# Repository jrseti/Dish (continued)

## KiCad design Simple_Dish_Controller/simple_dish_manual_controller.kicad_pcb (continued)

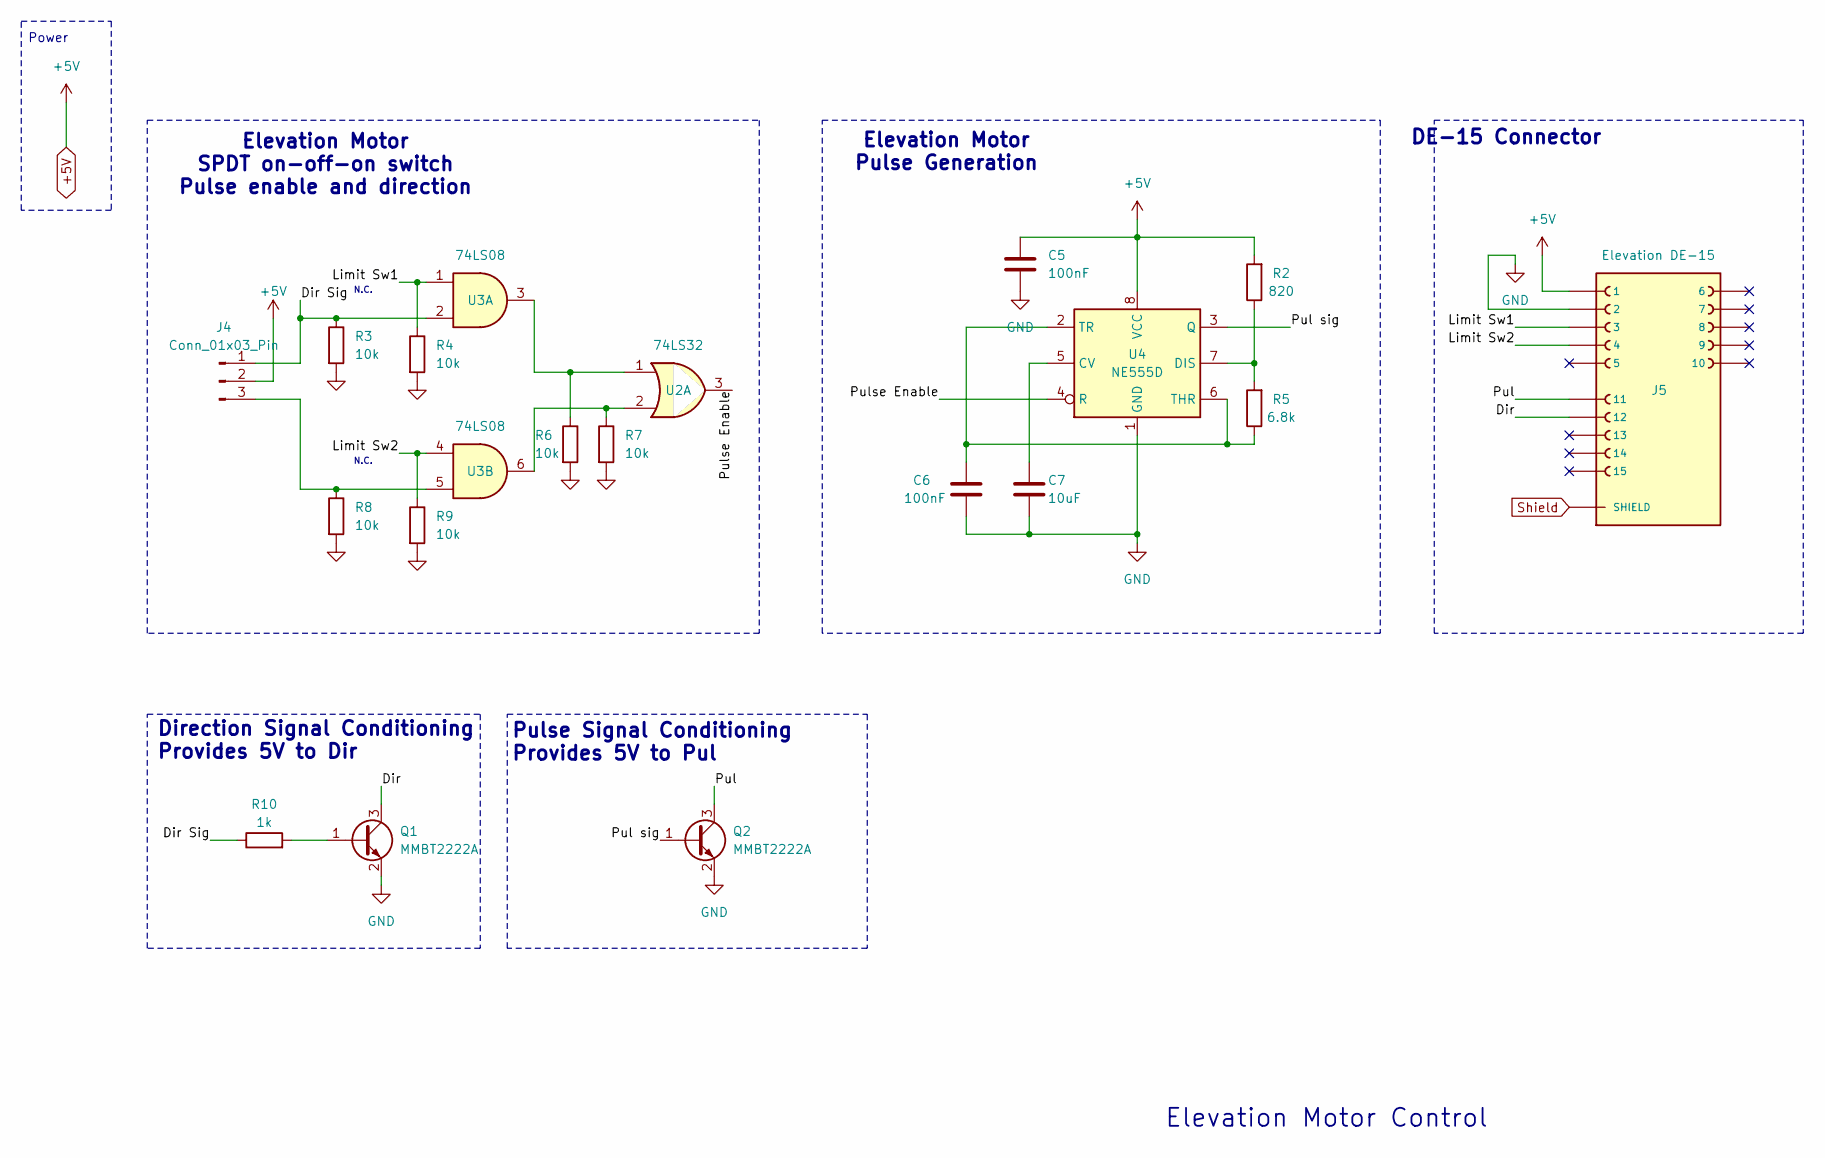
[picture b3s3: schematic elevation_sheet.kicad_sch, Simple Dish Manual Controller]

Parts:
C5, C6: 100nF; C_1206_3216Metric; LCSC Part C24497
C7: 10uF; C_1206_3216Metric; LCSC Part C13585
J4: Conn_01x03_Pin; PinHeader_1x03_P2.54mm_Vertical
J5: Elevation DE-15; DE15_VGA_FEMALE_CONN; PARTREV 1; DigiKey_Part_Number L77HDE15SD1CH4FVGA-ND
Q1, Q2: MMBT2222A; SOT-23; LCSC Part C8512
R2: 820; R_1206_3216Metric; LCSC Part C17984
R3, R4, R6, R7, R8, R9: 10k; R_1206_3216Metric; LCSC Part C17902
R5: 6.8k; R_1206_3216Metric; LCSC Part C2907522
R10: 1k; R_1206_3216Metric; LCSC Part C4410
U2: 74LS32; SOIC-14_3.9x8.7mm_P1.27mm; LCSC Part C116812
U3: 74LS08; SOIC-14_3.9x8.7mm_P1.27mm; LCSC Part C6802
U4: NE555D; SOIC-8_3.9x4.9mm_P1.27mm; LCSC Part C234230

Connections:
+5V: C5.1, J4.2, J5.1, R2.2, U4.8 (VCC); also elsewhere on the board
/Elevation/Dir: J5.12, Q1.3 (C)
/Elevation/Dir Sig: J4.1, R3.1, R10.1, U3.2
/Elevation/Limit Sw1: J5.3, R4.1, U3.1
/Elevation/Limit Sw2: J5.4, R9.1, U3.4
/Elevation/Pul: J5.11, Q2.3 (C)
/Elevation/Pul sig: Q2.1 (B), U4.3 (Q)
/Elevation/Pulse Enable: U2.3, U4.4 (R)
GND: C5.2, C6.2, C7.2, J5.2, Q1.2 (E), Q2.2 (E), R3.2, R4.2, R6.2, R7.2, R8.2, R9.2, U4.1 (GND); also elsewhere on the board
unnamed: J4.3, R8.1, U3.5
unnamed: Q1.1 (B), R10.2
unnamed: R6.1, U2.1, U3.3
unnamed: R7.1, U2.2, U3.6
unnamed: C7.1, U4.5 (CV)
unnamed: R2.1, R5.2, U4.7 (DIS)
unnamed: C6.1, R5.1, U4.2 (TR), U4.6 (THR)
Shield: J5.SH1 (SHIELD), J5.SH2 (SHIELD); also elsewhere on the board

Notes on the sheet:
DE-15 Connector
Elevation Motor Control
Power
N.C.
Pulse Signal Conditioning Provides 5V to Pul
Elevation Motor SPDT on-off-on switch Pulse enable and direction
Elevation Motor Pulse Generation
Direction Signal Conditioning Provides 5V to Dir

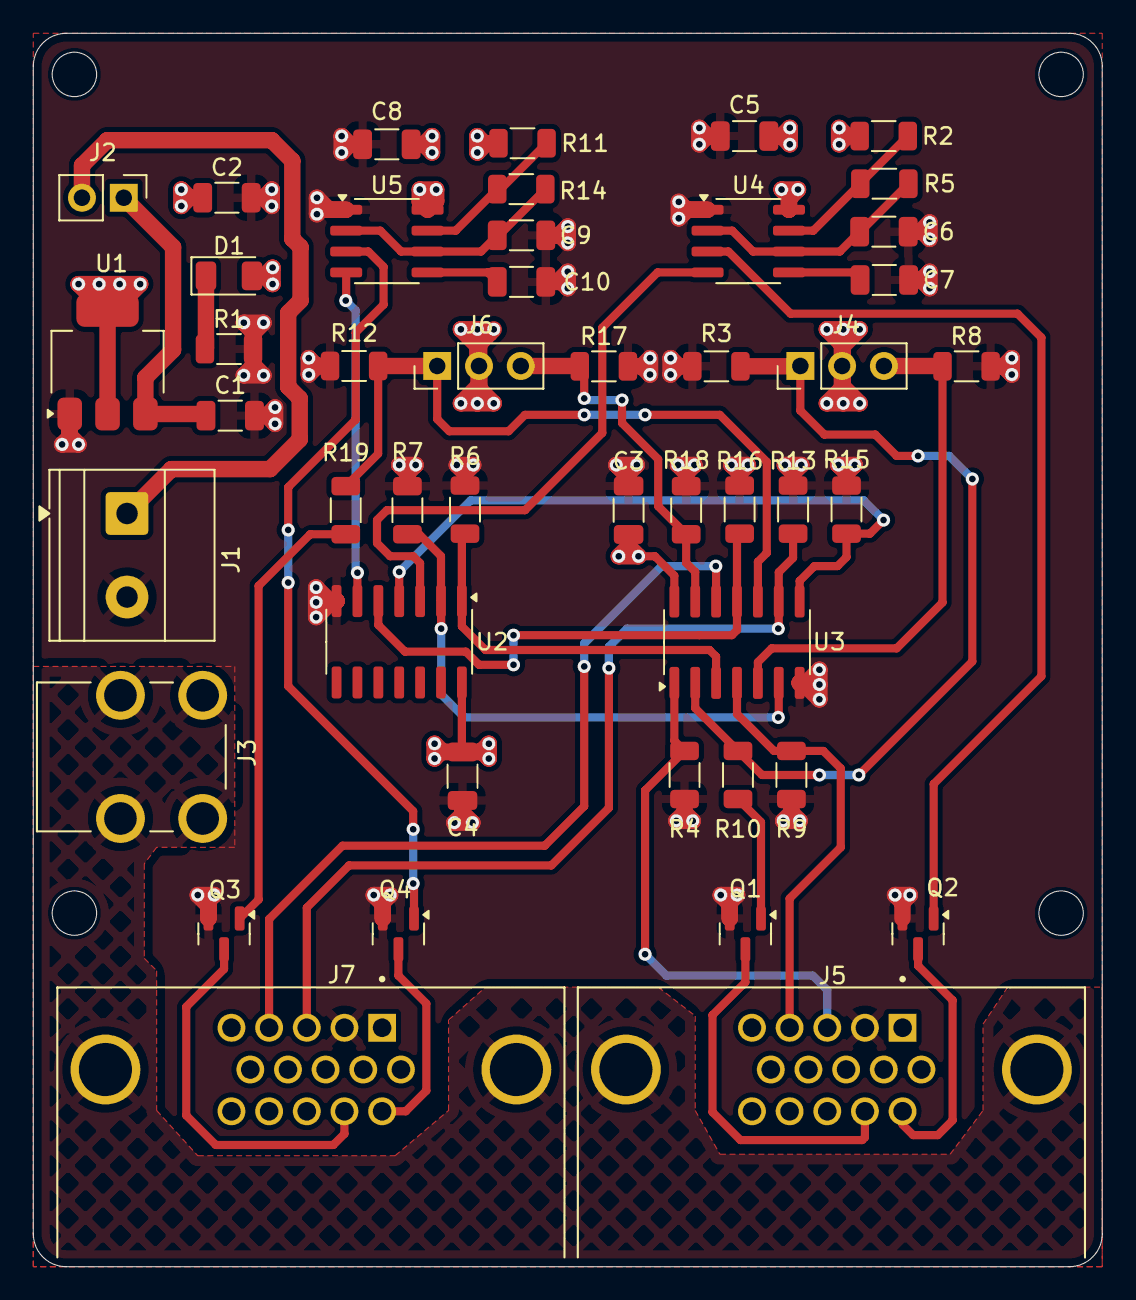
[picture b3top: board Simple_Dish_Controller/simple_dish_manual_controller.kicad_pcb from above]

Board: 4 copper layers, 65.0 x 75.0 mm, 50 parts (0 on the bottom side), 34 nets.

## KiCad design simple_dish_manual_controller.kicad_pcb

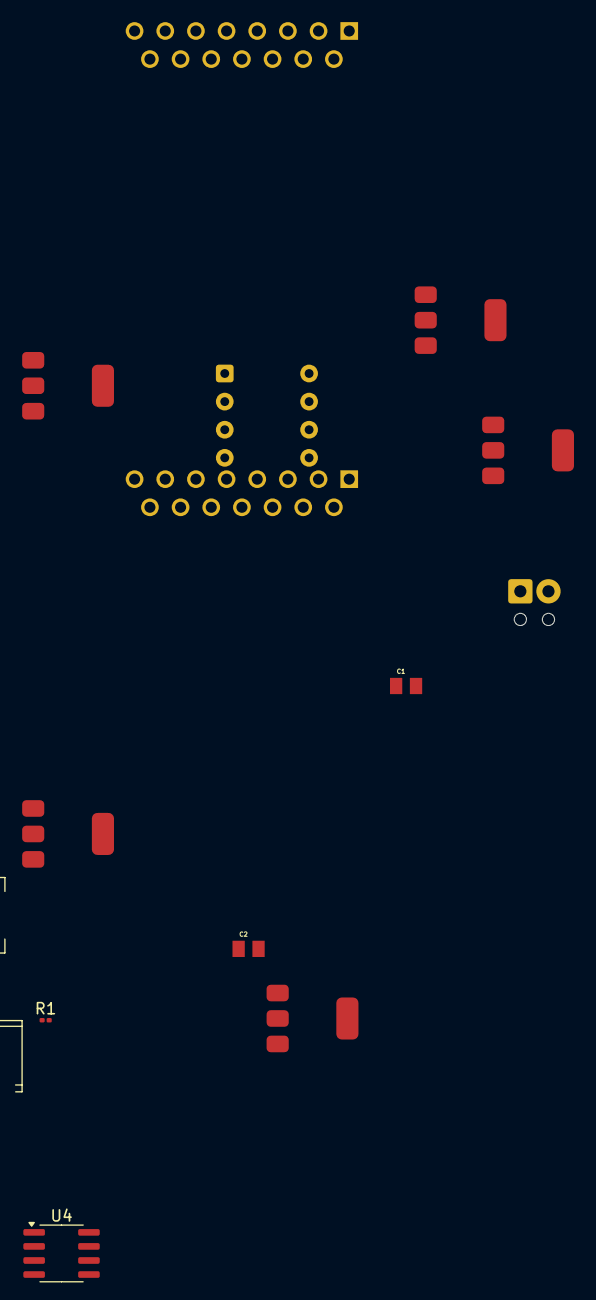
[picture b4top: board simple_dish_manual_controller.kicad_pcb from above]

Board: 2 copper layers, 13 parts (0 on the bottom side), 11 nets, no tracks yet.

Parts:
C1, C2: 22uF; CAPC2012X100N
J1: Screw_Terminal_01x02; TerminalBlock_Phoenix_MPT-0,5-2-2.54_1x02_P2.54mm_Horizontal
J2, J3: DA15_Socket; DSUB-15_Socket_Horizontal_P2.77x2.54mm_EdgePinOffset9.40mm
Q1, Q2, Q3, Q4: PZT2222A; SOT-223-3_TabPin2
R1: 1k5; R_0201_0603Metric
U1: AMS1117-5.0; SOT-223-3_TabPin2
U4: ICM7555xP; SOIC-8_3.9x4.9mm_P1.27mm
U5: ICM7555xP; DIP-8_W7.62mm

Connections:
+5V: C2.2, J2.5, J2.8, J3.5, J3.8, U1.2 (VO), U4.8 (VCC), U5.8 (VCC)
/Azimuth/Dir: J3.9, Q3.2 (C)
/Azimuth/Pul: J3.2, Q4.2 (C)
/Elevation/Dir: J2.9, Q2.2 (C)
/Elevation/Pul: J2.2, Q1.2 (C)
/IN_5VDC_SWITCH: C1.2, U1.3 (VI)
GND: C1.1, C2.1, J1.2, J2.1, J2.15, J3.1, J3.15, Q1.3 (E), Q2.3 (E), Q3.3 (E), Q4.3 (E), R1.2, U1.1 (GND), U4.1 (GND), U5.1 (GND)
unnamed: Q1.1 (B), U4.3 (Q)
unnamed: Q4.1 (B), U5.3 (Q)
unnamed: U4.2 (TR), U4.6 (THR)
unnamed: U5.2 (TR), U5.6 (THR)

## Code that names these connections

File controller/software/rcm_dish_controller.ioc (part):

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Mcu.Name=STM32G474R(B-C-E)Tx
Mcu.Package=LQFP64
Mcu.UserName=STM32G474RETx
PA0.GPIOParameters=GPIO_Label
PA0.GPIO_Label=ENC1_A
PA0.Signal=S_TIM2_CH1
PA1.GPIOParameters=GPIO_Label
PA1.GPIO_Label=ENC1_B
PA1.Signal=S_TIM2_CH2
PA10.GPIOParameters=GPIO_PuPd,GPIO_Label
PA10.GPIO_Label=SW2
PA10.GPIO_PuPd=GPIO_PULLUP
PA10.Signal=GPIO_Input
PA11.Mode=FDCAN_Activate
PA11.Signal=FDCAN1_RX
PA12.Mode=FDCAN_Activate
PA12.Signal=FDCAN1_TX
PA13.Mode=Trace_Asynchronous_SW
PA13.Signal=SYS_JTMS-SWDIO
PA14.Mode=Trace_Asynchronous_SW
PA14.Signal=SYS_JTCK-SWCLK
PA15.GPIOParameters=GPIO_PuPd,GPIO_Label
PA15.GPIO_Label=USER_SW_4
PA15.GPIO_PuPd=GPIO_PULLUP
PA15.Signal=GPIO_Input
PA2.GPIOParameters=GPIO_PuPd,GPIO_Label
PA2.GPIO_Label=ENC1_Z
PA2.GPIO_PuPd=GPIO_PULLUP
PA2.Signal=GPXTI2
PA3.GPIOParameters=GPIO_PuPd,GPIO_Label
PA3.GPIO_Label=LIMIT1_SW1
PA3.GPIO_PuPd=GPIO_PULLUP
PA3.Signal=GPIO_Input
PA4.GPIOParameters=GPIO_PuPd,GPIO_Label
PA4.GPIO_Label=LIMIT1_SW2
PA4.GPIO_PuPd=GPIO_PULLUP
PA4.Signal=GPIO_Input
PA5.GPIOParameters=GPIO_PuPd,GPIO_Label
PA5.GPIO_Label=LIMIT2_SW1
PA5.GPIO_PuPd=GPIO_PULLUP
PA5.Signal=GPIO_Input
PA6.GPIOParameters=GPIO_Label
PA6.GPIO_Label=PUL1
PA6.Signal=S_TIM16_CH1
PA7.GPIOParameters=GPIO_PuPd,GPIO_Label
PA7.GPIO_Label=LIMIT2_SW2
PA7.GPIO_PuPd=GPIO_PULLUP
PA7.Signal=GPIO_Input
PA8.GPIOParameters=GPIO_PuPd,GPIO_Label
PA8.GPIO_Label=SW4
PA8.GPIO_PuPd=GPIO_PULLUP
PA8.Signal=GPIO_Input
PA9.GPIOParameters=GPIO_PuPd,GPIO_Label
PA9.GPIO_Label=SW3
PA9.GPIO_PuPd=GPIO_PULLUP
PA9.Signal=GPIO_Input
PB0.GPIOParameters=GPIO_Label
PB0.GPIO_Label=PUL2
PB0.Signal=S_TIM3_CH3
PB1.GPIOParameters=GPIO_Label
PB1.GPIO_Label=DIR2
PB1.Signal=GPIO_Output
PB10.GPIOParameters=GPIO_Label
PB10.GPIO_Label=GPS_RX_MCU
PB10.Mode=Asynchronous
PB10.Signal=LPUART1_RX
PB11.GPIOParameters=GPIO_Label
PB11.GPIO_Label=GPS_TX_MCU
PB11.Mode=Asynchronous
PB11.Signal=LPUART1_TX
PB12.GPIOParameters=GPIO_Speed,GPIO_Label,GPIO_ModeDefaultOutputPP
PB12.GPIO_Label=FLASH_CS
PB12.GPIO_ModeDefaultOutputPP=GPIO_MODE_OUTPUT_PP
PB12.GPIO_Speed=GPIO_SPEED_FREQ_HIGH
PB12.Signal=GPIO_Output
PB13.Mode=Full_Duplex_Master
PB13.Signal=SPI2_SCK
PB14.Mode=Full_Duplex_Master
PB14.Signal=SPI2_MISO
PB15.Mode=Full_Duplex_Master
PB15.Signal=SPI2_MOSI
PB2.GPIOParameters=GPIO_Label
PB2.GPIO_Label=ENABLE2
PB2.Signal=GPIO_Output
PB3.Mode=Trace_Asynchronous_SW
PB3.Signal=SYS_JTDO-SWO
PB4.GPIOParameters=GPIO_Label
PB4.GPIO_Label=FAN
PB4.Signal=GPIO_Output
PB6.GPIOParameters=GPIO_Label
PB6.GPIO_Label=CM4_TX
PB6.Mode=Asynchronous
PB6.Signal=USART1_TX
PB7.GPIOParameters=GPIO_Label
PB7.GPIO_Label=CM4_RX
PB7.Mode=Asynchronous
PB7.Signal=USART1_RX
PB9.GPIOParameters=GPIO_Label
PB9.GPIO_Label=GPS_1PPS
PB9.Signal=S_TIM17_CH1
PC0.GPIOParameters=GPIO_Label
PC0.GPIO_Label=ENC2_A
PC0.Signal=S_TIM1_CH1
PC1.GPIOParameters=GPIO_Label
PC1.GPIO_Label=ENC2_B
PC1.Signal=S_TIM1_CH2
PC10.GPIOParameters=GPIO_PuPd,GPIO_Label
PC10.GPIO_Label=SW1
PC10.GPIO_PuPd=GPIO_PULLUP
PC10.Signal=GPIO_Input
PC11.GPIOParameters=GPIO_Label
PC11.GPIO_Label=STATUS_LED
PC11.Signal=GPIO_Output
PC2.GPIOParameters=GPIO_PuPd,GPIO_Label
PC2.GPIO_Label=USER_SW_1
PC2.GPIO_PuPd=GPIO_PULLUP
PC2.Signal=GPIO_Input
PC3.GPIOParameters=GPIO_PuPd,GPIO_Label
PC3.GPIO_Label=ENC2_Z
PC3.GPIO_PuPd=GPIO_PULLUP
PC3.Signal=GPXTI3
PC4.GPIOParameters=GPIO_Label
PC4.GPIO_Label=DIR1
PC4.Signal=GPIO_Output
PC5.GPIOParameters=GPIO_Label
PC5.GPIO_Label=ENABLE1
PC5.Signal=GPIO_Output
PC6.Mode=I2C
PC6.Signal=I2C4_SCL
PC7.Mode=I2C
PC7.Signal=I2C4_SDA
PC8.GPIOParameters=GPIO_PuPd,GPIO_Label
PC8.GPIO_Label=USER_SW_2
PC8.GPIO_PuPd=GPIO_PULLUP
PC8.Signal=GPIO_Input
PC9.GPIOParameters=GPIO_PuPd,GPIO_Label
PC9.GPIO_Label=USER_SW_3
PC9.GPIO_PuPd=GPIO_PULLUP
PC9.Signal=GPIO_Input
PD2.GPIOParameters=GPIO_PuPd,GPIO_Label,GPIO_ModeDefaultOutputPP
PD2.GPIO_Label=MCU_nIRQ
PD2.GPIO_ModeDefaultOutputPP=GPIO_MODE_OUTPUT_OD
PD2.GPIO_PuPd=GPIO_NOPULL
PD2.Signal=GPIO_Output
PF0-OSC_IN.Mode=HSE-External-Oscillator
PF0-OSC_IN.Signal=RCC_OSC_IN
PF1-OSC_OUT.Mode=HSE-External-Oscillator
PF1-OSC_OUT.Signal=RCC_OSC_OUT
RCC.HSE_VALUE=16000000
RCC.SYSCLKFreq_VALUE=170000000
RCC.SYSCLKSource=RCC_SYSCLKSOURCE_PLLCLK
board=custom

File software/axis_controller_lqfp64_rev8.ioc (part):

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Mcu.Name=STM32G474R(B-C-E)Tx
Mcu.Package=LQFP64
Mcu.UserName=STM32G474RETx
PA0.GPIOParameters=GPIO_Label
PA0.GPIO_Label=ENC1_A
PA0.Signal=S_TIM2_CH1
PA1.GPIOParameters=GPIO_Label
PA1.GPIO_Label=ENC1_B
PA1.Signal=S_TIM2_CH2
PA2.GPIOParameters=GPIO_PuPd,GPIO_Label
PA2.GPIO_Label=ENC1_Z
PA2.GPIO_PuPd=GPIO_PULLUP
PA2.Signal=GPXTI2
PA3.GPIOParameters=GPIO_PuPd,GPIO_Label
PA3.GPIO_Label=LIMIT1_SW1
PA3.GPIO_PuPd=GPIO_PULLUP
PA3.Signal=GPIO_Input
PA4.GPIOParameters=GPIO_PuPd,GPIO_Label
PA4.GPIO_Label=LIMIT1_SW2
PA4.GPIO_PuPd=GPIO_PULLUP
PA4.Signal=GPIO_Input
PA5.GPIOParameters=GPIO_Label
PA5.GPIO_Label=ENABLE2
PA5.Signal=GPIO_Output
PA6.GPIOParameters=GPIO_PuPd,GPIO_Label
PA6.GPIO_Label=LIMIT2_SW1
PA6.GPIO_PuPd=GPIO_PULLUP
PA6.Signal=GPIO_Input
PA7.GPIOParameters=GPIO_PuPd,GPIO_Label
PA7.GPIO_Label=LIMIT2_SW2
PA7.GPIO_PuPd=GPIO_PULLUP
PA7.Signal=GPIO_Input
PA8.GPIOParameters=GPIO_PuPd,GPIO_Label
PA8.GPIO_Label=CONFIG_SW
PA8.GPIO_PuPd=GPIO_PULLUP
PA8.Signal=GPIO_Input
PA9.GPIOParameters=GPIO_PuPd,GPIO_Label
PA9.GPIO_Label=ADDR2
PA9.GPIO_PuPd=GPIO_PULLUP
PA9.Signal=GPIO_Input
PA10.GPIOParameters=GPIO_PuPd,GPIO_Label
PA10.GPIO_Label=ADDR1
PA10.GPIO_PuPd=GPIO_PULLUP
PA10.Signal=GPIO_Input
PA11.GPIOParameters=GPIO_PuPd,GPIO_Label
PA11.GPIO_Label=ADDR0
PA11.GPIO_PuPd=GPIO_PULLUP
PA11.Signal=GPIO_Input
PA12.GPIOParameters=GPIO_Label
PA12.GPIO_Label=STATUS_LED
PA12.Signal=GPIO_Output
PA13.Mode=Trace_Asynchronous_SW
PA13.Signal=SYS_JTMS-SWDIO
PA14.Mode=Trace_Asynchronous_SW
PA14.Signal=SYS_JTCK-SWCLK
PB0.GPIOParameters=GPIO_Label
PB0.GPIO_Label=PUL
PB0.Signal=S_TIM3_CH3
PB1.GPIOParameters=GPIO_Label
PB1.GPIO_Label=DIR
PB1.Signal=GPIO_Output
PB2.GPIOParameters=GPIO_Label
PB2.GPIO_Label=ENABLE
PB2.Signal=GPIO_Output
PB3.Mode=Trace_Asynchronous_SW
PB3.Signal=SYS_JTDO-SWO
PB5.GPIOParameters=GPIO_Label
PB5.GPIO_Label=RS485_HOST_DE
PB5.Signal=GPIO_Output
PB6.Mode=Asynchronous
PB6.Signal=USART1_TX
PB7.Mode=Asynchronous
PB7.Signal=USART1_RX
PB8.Signal=GPIO_Input
PB9.GPIOParameters=GPIO_PuPd,GPIO_Label
PB9.GPIO_Label=GPS_1PPS
PB9.GPIO_PuPd=GPIO_PULLDOWN
PB9.Signal=GPXTI9
PB10.Mode=Asynchronous
PB10.Signal=LPUART1_RX
PB11.Mode=Asynchronous
PB11.Signal=LPUART1_TX
PB12.GPIOParameters=GPIO_Label,GPIO_ModeDefaultOutputPP,GPIO_Speed
PB12.GPIO_Label=FLASH_CS
PB12.GPIO_ModeDefaultOutputPP=GPIO_MODE_OUTPUT_PP
PB12.GPIO_Speed=GPIO_SPEED_FREQ_HIGH
PB12.Signal=GPIO_Output
PB13.Mode=Full_Duplex_Master
PB13.Signal=SPI2_SCK
PB14.Mode=Full_Duplex_Master
PB14.Signal=SPI2_MISO
PB15.Mode=Full_Duplex_Master
PB15.Signal=SPI2_MOSI
PC0.GPIOParameters=GPIO_Label
PC0.GPIO_Label=ENC2_A
PC0.Signal=S_TIM1_CH1
PC1.GPIOParameters=GPIO_Label
PC1.GPIO_Label=ENC2_B
PC1.Signal=S_TIM1_CH2
PC3.GPIOParameters=GPIO_PuPd,GPIO_Label
PC3.GPIO_Label=ENC2_Z
PC3.GPIO_PuPd=GPIO_PULLUP
PC3.Signal=GPXTI3
PC6.Mode=I2C
PC6.Signal=I2C4_SCL
PC7.Mode=I2C
PC7.Signal=I2C4_SDA
PC8.GPIOParameters=GPIO_Label
PC8.GPIO_Label=PUL2
PC8.Signal=S_TIM8_CH3
PC9.GPIOParameters=GPIO_Label
PC9.GPIO_Label=DIR2
PC9.Signal=GPIO_Output
PC10.Mode=Asynchronous
PC10.Signal=USART3_TX
PC11.Mode=Asynchronous
PC11.Signal=USART3_RX
PC13.GPIOParameters=GPIO_Label
PC13.GPIO_Label=FAN
PC13.Signal=GPIO_Output
PD2.GPIOParameters=GPIO_Label
PD2.GPIO_Label=RS485_LEAD_DE
PD2.Signal=GPIO_Output
PF0-OSC_IN.Mode=HSE-External-Oscillator
PF0-OSC_IN.Signal=RCC_OSC_IN
PF1-OSC_OUT.Mode=HSE-External-Oscillator
PF1-OSC_OUT.Signal=RCC_OSC_OUT
PG10-NRST.Signal=SYS_RESET
RCC.HSE_VALUE=16000000
RCC.SYSCLKFreq_VALUE=170000000
board=custom

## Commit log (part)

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2025-03-03 Added Kicad project files
2025-03-03 Added overview diagram
2025-03-03 Added to README
2025-03-03 Changed image size to 800
2025-03-18 Simple changes
2025-03-19 Breaking up into sheets
2025-03-19 Broken into sheets
2025-03-20 Elevation sheet mostly complete
2025-03-21 Added Azimuth
2025-03-22 New drawing
2025-03-23 Latest versions
2025-03-23 Updated C1 cap part path
2025-03-23 Readme edit
2025-03-23 Added RJ45 ports
2025-03-23 Footprints defined - passes ERC
2025-03-23 777 chip is now SMD
2025-03-28 Added the parts directory
2025-03-28 Added parts dir
2025-03-28 Set up supplier_parts directory and default lib
2025-03-31 Still creating parts libraries
2025-03-31 Added utils/venv
2025-03-31 More parts defined
2025-04-04 Latest update
2025-04-15 Edited README
2025-04-15 Removed parts dir
2025-04-15 Added sym-lib-table and fp-lib-table
2025-04-15 Added back in fp-lib-table and sym-lib-table
2025-04-15 minor update to PCB
2025-04-16 Utility files documented and added
2025-04-16 Added venv and temp.txt
2025-04-17 Removed submodule completely
2025-04-17 Added back submodule
2025-04-17 Added submodule
2025-04-17 Removed submodule
2025-04-17 Spellign correction
2025-04-18 Added Dish_Interface_Board
2025-04-18 Started schematic
2025-04-18 PCB outline defined, origin and drill holes established, hole positioning completed. Beginning component placement.
2025-04-22 Component placement
2025-04-24 Component placement and added traces
2025-04-24 Final version of the PCB.Production files were generated in -Production- folder
